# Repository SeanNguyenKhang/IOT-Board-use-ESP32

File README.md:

# IOT-Board-use-ESP32
An ESP32-WROOM-32E WiFi MCU-based board, featuring a USB-style pin header for SHT3x temperature and humidity sensor integration, and a dedicated interface for DWIN HMI displays. Design in Kicad.

# Key Features
- ESP32-WROOM-32E MCU.
- Module Hi-Link HLK-5M05 to convert 220VAC - 5VDC.
- On-board relay for AC load control.
- Header for SHT3x sensor.
- Module Ra-02 LoRa and header for HMI display.
- USB connector for power and programming.
# Applications
This board can be used for:
- Smart Home Controller.
- Smart Switch.
- IoT Environmental Monitoring.
- Remote Device Control.
- Industrial IoT Node.
# Development Tools
Recommended tools:
- KiCad (PCB Design).
- VSCode with IDF Enviroment.
- Arduino Framework.

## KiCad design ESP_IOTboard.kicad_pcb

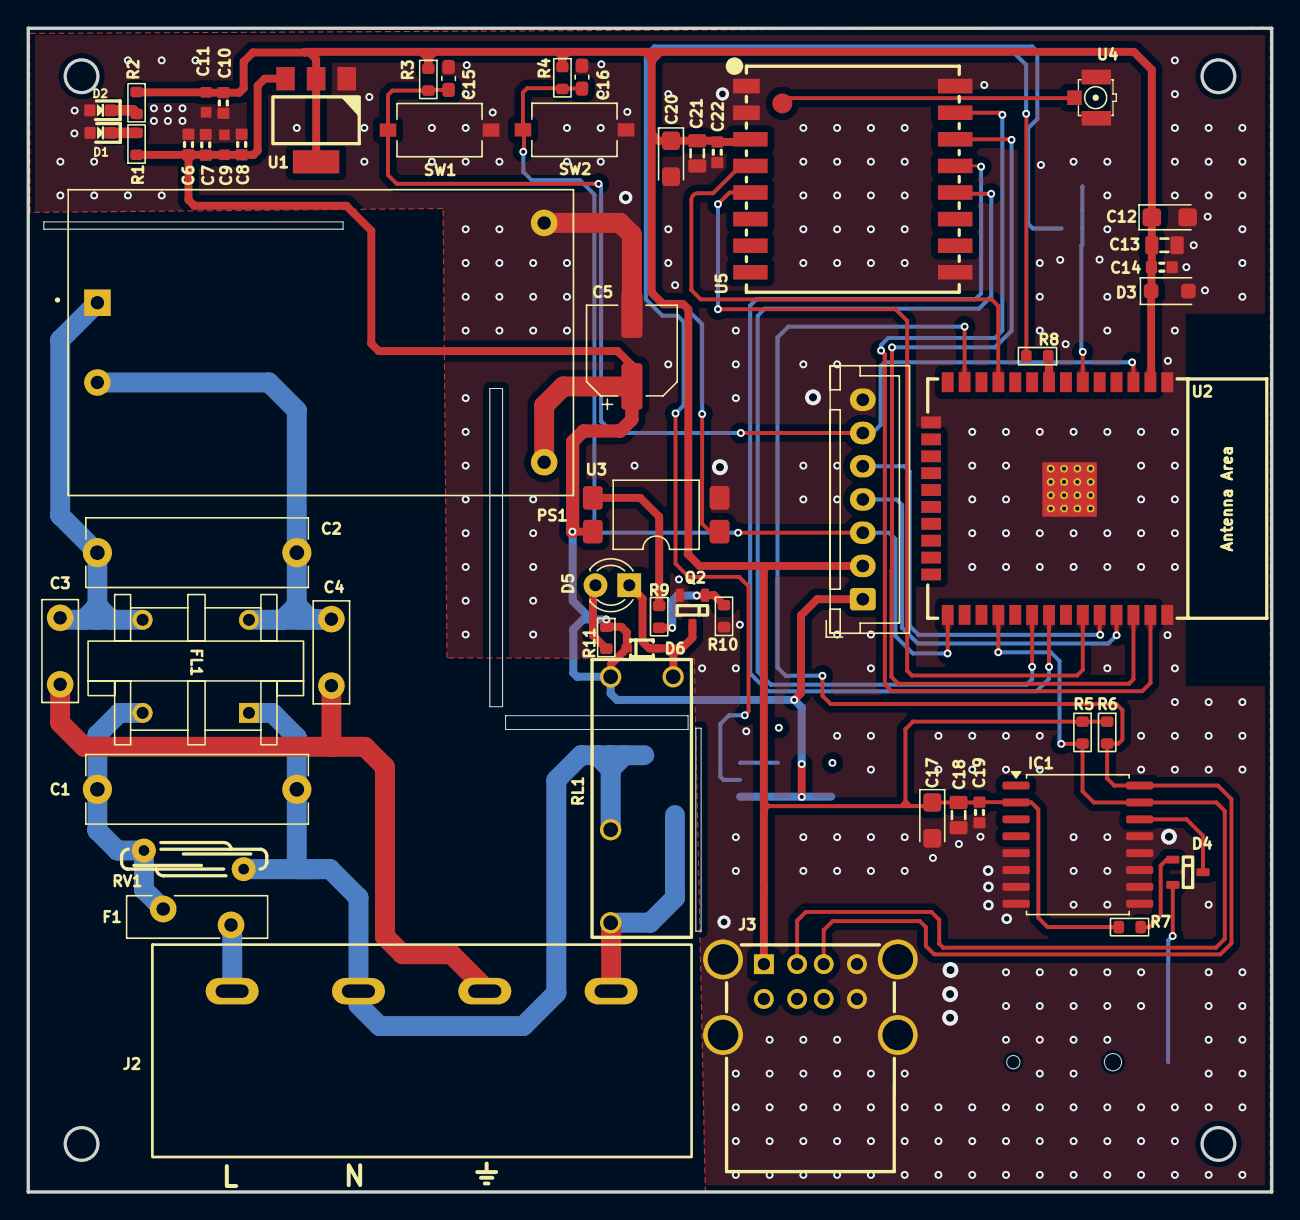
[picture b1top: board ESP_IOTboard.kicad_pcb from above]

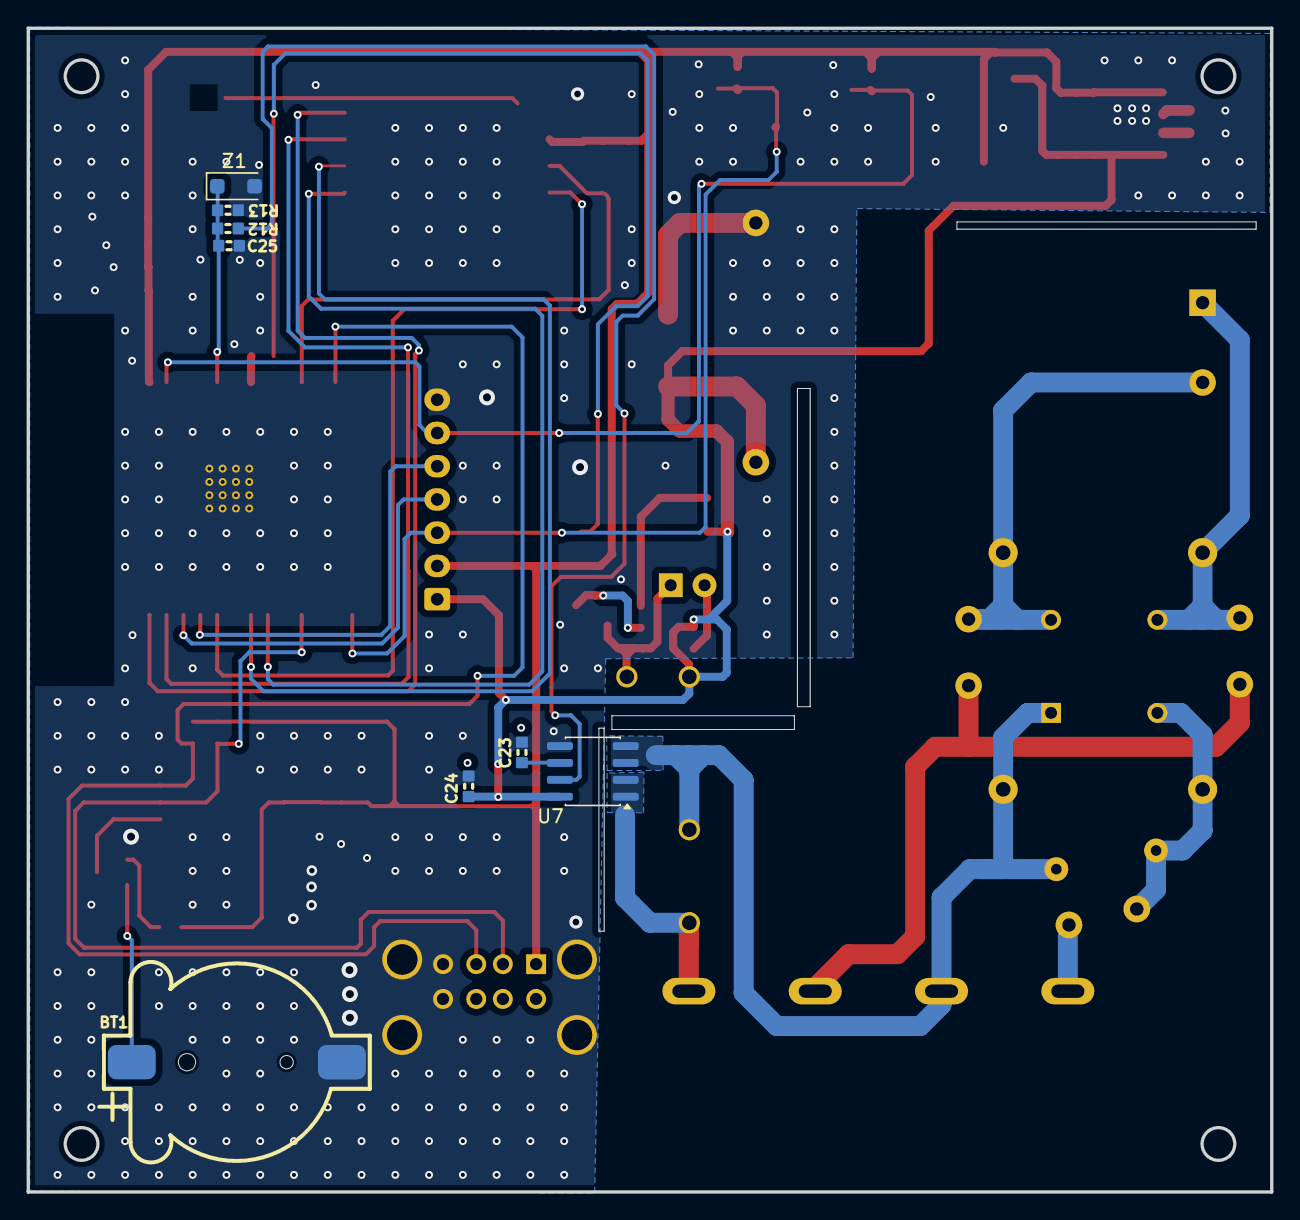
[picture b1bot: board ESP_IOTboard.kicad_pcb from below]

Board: 2 copper layers, 93.5 x 87.5 mm, 64 parts (8 on the bottom side), 37 nets.

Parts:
BT1: CR1220; BatteryHolder_CR1220
C1: 0.1uF/ 275VAC; C_Rect_L16.5mm_W5.0mm_P15.00mm_MKT
C2: 0.1uF/275VAC; C_Rect_L16.5mm_W5.0mm_P15.00mm_MKT
C3, C4: 10nF/1000VAC; C_Disc_D7.5mm_W2.5mm_P5.00mm
C5: 220uF/6.3x7.7/6.3V; CP_Elec_6.3x7.7
C6, C8, C10: 10uF/0603/6.3V; C_0603
C7, C14, C19, C22, C24: 100nF/0603/50V; C_0603
C9, C11: 100nF/0603/50V; SMD-0603C
C12, C17, C20: 100uF/3216/16V; CP_EIA-3216-10_Kemet-I
C13, C18, C21: 1uF/0805/25V; C_0805
C15, C16: 10uF/0603/50V; C_0603_1608Metric_Pad1.08x0.95mm_HandSolder
C23: 100nF/0603; C_0603
C25: 10nF/0603; C_0603
D1: RED/0603; LED_0603
D2: GREEN/0603; LED_0603
D3: BZT52Bxx; D_SOD-123F
D4: BAT54C; SOT23-3
D5: RED/0603; LED_D3.0mm_Red
D6: 1N4148WS; D_SOD323
F1: 300mA/250VAC; Fuse_Bourns_MF-RG500
FL1: 10mH/UU9.8 103; ACFilterChokeUU9.8
IC1: RTC_DS3231M; SOIC-16W_7.5x10.3mm_P1.27mm
J1: Conn_01x07_Pin; JST_XH_B7B-XH-A_1x07_P2.50mm_Vertical
J2: HP 9500; TerminalBlock_Screw_HB9500_4P_P9.5mm
J3: USB_A_Stacked; USB_A_Wuerth_61400826021_Horizontal_Stacked
PS1: HLK-10M05; HLK-5M05
Q2: N_Mosfet; SOT23-3
R1, R2: 2.2K/0603/5%; R_0603_1608Metric
R3, R4, R10: 10K/0603/5%; R_0603_1608Metric
R5, R6: 4.7K/0603/1%; R_0603_1608Metric
R7: 1K/0603/1%; R_0603_1608Metric
R8: 1K/0603/5%; R_0603_1608Metric
R9: 100/0603/5%; R_0603_1608Metric
R11: 470/0603/5%; R_0603_1608Metric
R12: 4.7K/0603/1%; R_0603
R13: 1.2K/0603/1%; R_0603
RL1: Relay_G5NB-1A-E_DC5; Relay_G5NB-1A-E DC5
RV1: 560V; RV_Disc_D12mm_W3.9mm_P7.5mm
SW1: Reset_button; SW_Tactile_SPST_NO_Straight_CK_PTS636Sx25SMTRLFS
SW2: Boot_button; SW_Tactile_SPST_NO_Straight_CK_PTS636Sx25SMTRLFS
U1: AMS1117 - 3.3/SOT-223; SOT233
U2: ESP32-WROOM-32E
U3: EL357N; SMDIP-4_W9.53mm_Clearance8mm
U4: Ipex; IPEX_Antena_Connector
U5: Ai-Thinker-Ra-02; MODULE_RA-02_LORA
U7: ACS712xLCTR-20A; SOIC-8_3.9x4.9mm_P1.27mm
Z1: 3V6; D_SOD-123F

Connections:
+3V3: C10.1, C11.1, C12.1, C13.1, C14.1, C17.1, C18.1, C19.1, C20.1, C21.1, C22.1, D3.1 (K), IC1.2 (VCC), J1.2, J3.1 (VBUS1), R2.1, R3.1, R4.1, R5.1, R6.1, R7.1, U1.2 (VO), U2.2 (VDD), U5.3 (VDD)
+5V: C5.1, C6.1, C7.1, C8.1, C9.1, C24.1, D6.2, J1.1, PS1.4 (+Vout), R1.1, R11.1, RL1.1, U1.3 (VI), U3.4, U7.8 (VCC)
/MCU_ESP32_WROM_32E/ESP_BOOT: C16.1, J1.3, R4.2, SW2.1, U2.25 (IO0)
/MCU_ESP32_WROM_32E/ESP_RST: C15.1, J1.6, R3.2, SW1.1, U2.3 (EN)
/MCU_ESP32_WROM_32E/ESP_RX: J1.5, U2.34 (RXD0/IO3)
/MCU_ESP32_WROM_32E/ESP_TX: J1.4, U2.35 (TXD0/IO1)
/MCU_ESP32_WROM_32E/I2C_SCL: IC1.16 (SCL), J3.3 (D1+), R6.2, U2.13 (IO14)
/MCU_ESP32_WROM_32E/I2C_SDA: IC1.15 (SDA), J3.2 (D1-), R5.2, U2.28 (IO17)
/MCU_ESP32_WROM_32E/LoRa.CS: U2.37 (IO23), U5.15 (~NSS)
/MCU_ESP32_WROM_32E/LoRa.INT: U2.33 (IO21), U5.5 (DIO0)
/MCU_ESP32_WROM_32E/LoRa.MISO: U2.31 (IO19), U5.13 (MISO)
/MCU_ESP32_WROM_32E/LoRa.MOSI: U2.36 (IO22), U5.14 (MOSI)
/MCU_ESP32_WROM_32E/LoRa.RST: U2.11 (IO26), U5.4 (~RESET)
/MCU_ESP32_WROM_32E/LoRa.SCK: U2.30 (IO18), U5.12 (SCK)
ADC: C25.1, R12.2, R13.2, U2.6 (IO34), Z1.1 (K)
Earth: C3.1, C4.2, J2.3
GND: BT1.2 (-), C5.2, C6.2, C7.2, C8.2, C9.2, C10.2, C11.2, C12.2, C13.2, C14.2, C15.2, C16.2, C17.2, C18.2, C19.2, C20.2, C21.2, C22.2, C23.2, C24.2, C25.2, D1.1 (K), D2.1 (K), D3.2 (A), IC1.5 (GND), IC1.6 (GND), IC1.7 (GND), IC1.8 (GND), IC1.9 (GND), IC1.10 (GND), IC1.11 (GND), IC1.12 (GND), IC1.13 (GND), J1.7, J3.4 (GND1), J3.8 (GND2), J3.9 (Shield), PS1.3 (-Vout), Q2.2 (S), R10.1, R13.1, SW1.2, SW2.2, U1.1 (GND), U2.1 (GND), U2.15 (GND), U2.38 (GND), U2.39 (GND), U3.2, U4.2, U5.1 (GND), U5.2 (GND), U5.9 (GND), U5.16 (GND), U7.5 (GND), Z1.2 (A)
LINE: F1.1, J2.1
NEUTRAL: C1.2, FL1.1, J2.2, RL1.2, RV1.1, U7.3 (IP-), U7.4 (IP-)
unnamed: BT1.1 (+), D4.2
unnamed: C1.1, F1.2, FL1.3, RV1.2
unnamed: D1.2 (A), R1.2
unnamed: D2.2 (A), R2.2
unnamed: D4.1, R7.2
unnamed: D5.2 (A), R11.2
unnamed: D5.1 (K), D6.1, Q2.3 (D), RL1.4
unnamed: D4.3, IC1.14 (VBAT)
unnamed: C2.1, C3.2, FL1.4, PS1.1 (AC/L)
unnamed: C2.2, C4.1, FL1.2, PS1.2 (AC/N)
unnamed: Q2.1 (G), R9.2, R10.2
unnamed: R8.2, U3.1
unnamed: R9.1, U3.3
unnamed: U4.1, U5.17 (Anaten)
unnamed: C23.1, U7.6 (FILTER)
unnamed: R12.1, U7.7 (VIOUT)
RELAY: J2.4, RL1.3, U7.1 (IP+), U7.2 (IP+)
RELAY_IN: R8.1, U2.8 (IO32)

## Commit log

2026-03-08 README.md
2026-03-08 image1.png
2026-03-08 image2.png
